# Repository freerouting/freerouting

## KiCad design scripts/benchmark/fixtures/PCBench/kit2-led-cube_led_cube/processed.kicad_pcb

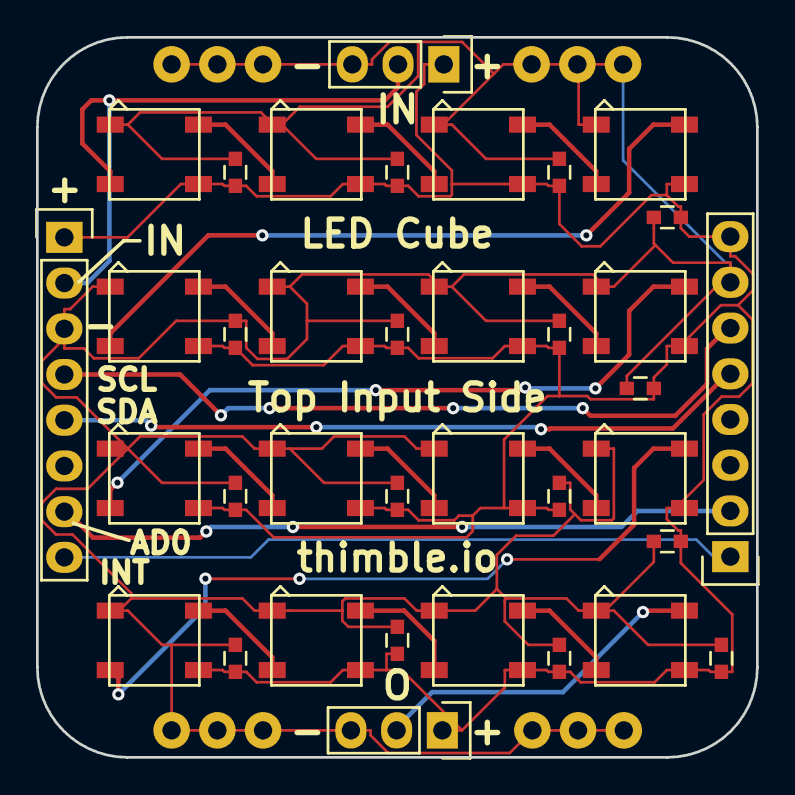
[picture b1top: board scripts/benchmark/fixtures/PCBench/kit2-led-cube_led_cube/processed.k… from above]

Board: 2 copper layers, 40.0 x 40.0 mm, 36 parts (0 on the bottom side), 23 nets.

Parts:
C1, C2, C3, C4, C5, C6, C7, C8, C9, C10, C11, C12, C13, C14, C15, C16: 1uF; C_0603
LED1, LED2, LED3, LED4, LED5, LED6, LED7, LED8, LED9, LED10, LED11, LED12, LED13, LED14, LED15, LED16: LED_RGB_WS2812B; 5050
P1, P4: CONN_01X03; Pin_Header_Straight_1x03
P2, P3: CONN_01X08; Pin_Header_Straight_1x08

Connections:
+5V: C1.1, C2.1, C3.1, C4.1, C5.1, C6.1, C7.1, C8.1, C9.1, C10.1, C11.1, C12.1, C13.1, C14.1, C15.1, C16.1, LED1.1, LED2.1, LED3.1, LED4.1, LED5.1, LED6.1, LED7.1, LED8.1, LED9.1, LED10.1, LED11.1, LED12.1, LED13.1, LED14.1, LED15.1, LED16.1, P1.1, P2.1, P3.8, P4.1
/AD0: P2.7, P3.2
/INT: P2.8, P3.1
/SCL: P2.4, P3.6
/SDA: P2.5, P3.5
GND: C1.2, C2.2, C3.2, C4.2, C5.2, C6.2, C7.2, C8.2, C9.2, C10.2, C11.2, C12.2, C13.2, C14.2, C15.2, C16.2, LED1.3, LED2.3, LED3.3, LED4.3, LED5.3, LED6.3, LED7.3, LED8.3, LED9.3, LED10.3, LED11.3, LED12.3, LED13.3, LED14.3, LED15.3, LED16.3, P1.3, P2.3, P3.7, P4.3
unnamed: LED1.2, LED2.4
unnamed: LED1.4, P1.2, P2.2
unnamed: LED2.2, LED3.4
unnamed: LED3.2, LED4.4
unnamed: LED4.2, LED5.4
unnamed: LED5.2, LED6.4
unnamed: LED6.2, LED7.4
unnamed: LED7.2, LED8.4
unnamed: LED8.2, LED9.4
unnamed: LED10.2, LED11.4
unnamed: LED9.2, LED10.4
unnamed: LED11.2, LED12.4
unnamed: LED12.2, LED13.4
unnamed: LED13.2, LED14.4
unnamed: LED14.2, LED15.4
unnamed: LED15.2, LED16.4
unnamed: LED16.2, P4.2

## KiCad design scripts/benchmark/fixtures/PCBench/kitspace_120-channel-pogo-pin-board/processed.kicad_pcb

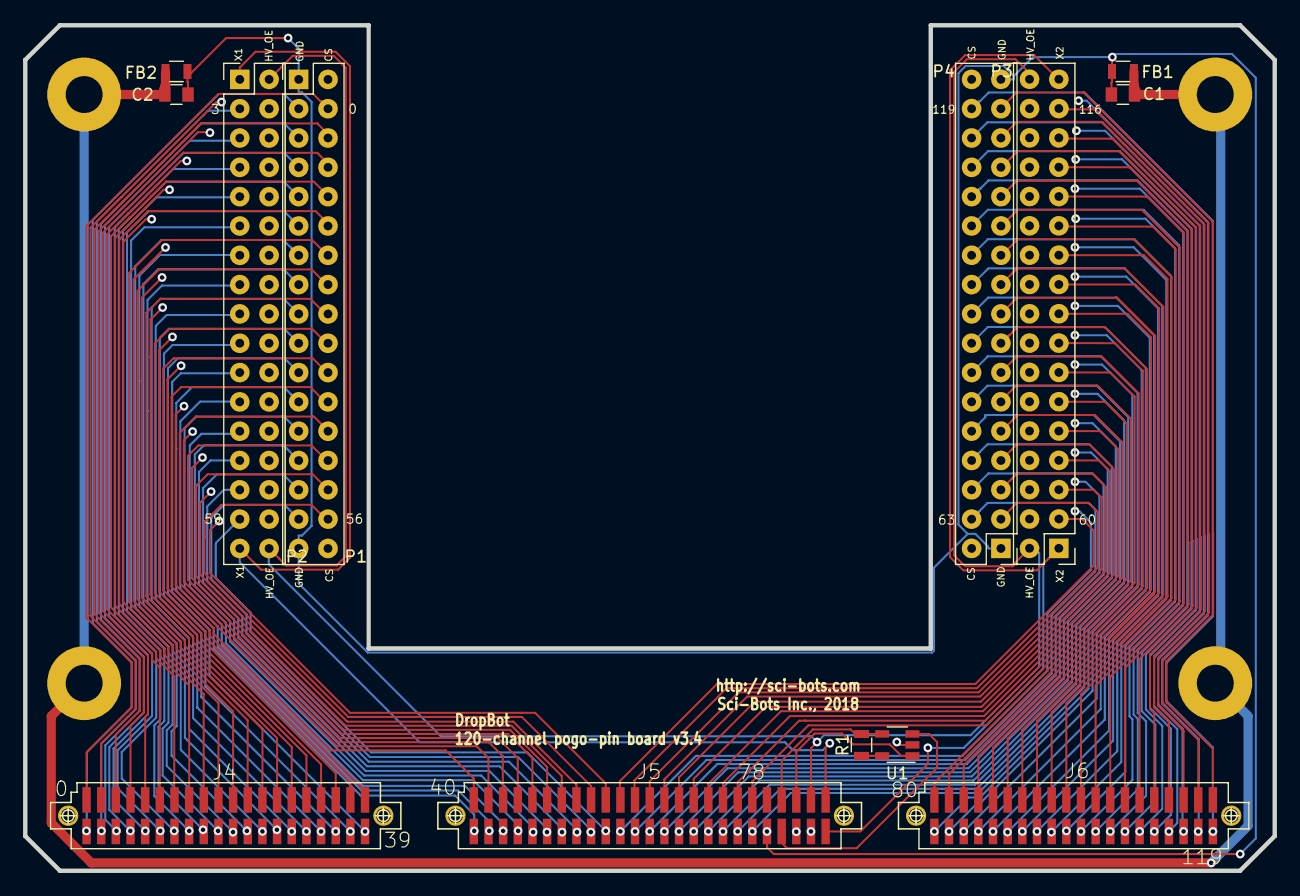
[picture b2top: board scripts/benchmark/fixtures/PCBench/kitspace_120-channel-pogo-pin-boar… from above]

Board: 4 copper layers, 108.2 x 73.2 mm, 17 parts (0 on the bottom side), 130 nets.

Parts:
C1, C2: 0.1uF; C_0805
FB1, FB2: FERRITE; R_0805
J4, J6: SFM-120-02-L-D-A; SFM-120-02-XXX-D-A
J5: SFM-125-02-L-D-A; SFM-125-02-XXX-D-A
P1, P2, P3, P4: Conn_02x17_Odd_Even; Pogo_Pin_Header_Straight_2x17_Pitch2.54mm
P5, P6, P7, P8: CONN_01X01; MountingHole_3.2mm_M3_Pad
R1: 10k; R_0805
U1: CAT24C02TDI; TSOT-23-5

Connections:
+3V3: J5.8, R1.2, U1.4
CH0: J4.40, P1.4
CH1: J4.39, P1.3
CH2: J4.38, P2.4
CH3: J4.37, P2.3
CH4: J4.36, P1.6
CH5: J4.35, P1.5
CH6: J4.34, P2.6
CH7: J4.33, P2.5
CH8: J4.32, P1.8
CH9: J4.31, P1.7
CH10: J4.30, P2.8
CH11: J4.29, P2.7
CH12: J4.28, P1.10
CH13: J4.27, P1.9
CH14: J4.26, P2.10
CH15: J4.25, P2.9
CH16: J4.24, P1.12
CH17: J4.23, P1.11
CH18: J4.22, P2.12
CH19: J4.21, P2.11
CH20: J4.20, P1.14
CH21: J4.19, P1.13
CH22: J4.18, P2.14
CH23: J4.17, P2.13
CH24: J4.16, P1.16
CH25: J4.15, P1.15
CH26: J4.14, P2.16
CH27: J4.13, P2.15
CH28: J4.12, P1.18
CH29: J4.11, P1.17
CH30: J4.10, P2.18
CH31: J4.9, P2.17
CH32: J4.8, P1.20
CH33: J4.7, P1.19
CH34: J4.6, P2.20
CH35: J4.5, P2.19
CH36: J4.4, P1.22
CH37: J4.3, P1.21
CH38: J4.2, P2.22
CH39: J4.1, P2.21
CH40: J5.50, P1.24
CH41: J5.49, P1.23
CH42: J5.48, P2.24
CH43: J5.47, P2.23
CH44: J5.46, P1.26
CH45: J5.45, P1.25
CH46: J5.44, P2.26
CH47: J5.43, P2.25
CH48: J5.42, P1.28
CH49: J5.41, P1.27
CH50: J5.40, P2.28
CH51: J5.39, P2.27
CH52: J5.38, P1.30
CH53: J5.37, P1.29
CH54: J5.36, P2.30
CH55: J5.35, P2.29
CH56: J5.34, P1.32
CH57: J5.33, P1.31
CH58: J5.32, P2.32
CH59: J5.31, P2.31
CH60: J5.30, P3.3
CH61: J5.29, P3.4
CH62: J5.28, P4.3
CH63: J5.27, P4.4
CH64: J5.26, P3.5
CH65: J5.25, P3.6
CH66: J5.24, P4.5
CH67: J5.23, P4.6
CH68: J5.22, P3.7
CH69: J5.21, P3.8
CH70: J5.20, P4.7
CH71: J5.19, P4.8
CH72: J5.18, P3.9
CH73: J5.17, P3.10
CH74: J5.16, P4.9
CH75: J5.15, P4.10
CH76: J5.14, P3.11
CH77: J5.13, P3.12
CH78: J5.12, P4.11
CH79: J5.11, P4.12
CH80: J6.40, P3.13
CH81: J6.39, P3.14
CH82: J6.38, P4.13
CH83: J6.37, P4.14
CH84: J6.36, P3.15
CH85: J6.35, P3.16
CH86: J6.34, P4.15
CH87: J6.33, P4.16
CH88: J6.32, P3.17
CH89: J6.31, P3.18
CH90: J6.30, P4.17
CH91: J6.29, P4.18
CH92: J6.28, P3.19
CH93: J6.27, P3.20
CH94: J6.26, P4.19
CH95: J6.25, P4.20
CH96: J6.24, P3.21
CH97: J6.23, P3.22
CH98: J6.22, P4.21
CH99: J6.21, P4.22
CH100: J6.20, P3.23
CH101: J6.19, P3.24
CH102: J6.18, P4.23
CH103: J6.17, P4.24
CH104: J6.16, P3.25
CH105: J6.15, P3.26
CH106: J6.14, P4.25
CH107: J6.13, P4.26
CH108: J6.12, P3.27
CH109: J6.11, P3.28
CH110: J6.10, P4.27
CH111: J6.9, P4.28
CH112: J6.8, P3.29
CH113: J6.7, P3.30
CH114: J6.6, P4.29
CH115: J6.5, P4.30
CH116: J6.4, P3.31
CH117: J6.3, P3.32
CH118: J6.2, P4.31
CH119: J6.1, P4.32
CH-X1: J5.2, P2.1, P2.33
CH-X2: J5.1, P3.1, P3.33
CHASIS_GND: C1.2, C2.2, FB1.2, FB2.2, P5.1, P6.1, P7.1, P8.1
CUR_SENSE: J5.3, P1.2, P1.34, P4.2, P4.34
GND: C1.1, C2.1, FB1.1, FB2.1, J5.5, J5.9, P1.1, P1.33, P4.1, P4.33, U1.2
HV_OE: J5.4, P2.2, P2.34, P3.2, P3.34
unnamed: R1.1, U1.5
SCL: J5.6, U1.1
SDA: J5.7, U1.3

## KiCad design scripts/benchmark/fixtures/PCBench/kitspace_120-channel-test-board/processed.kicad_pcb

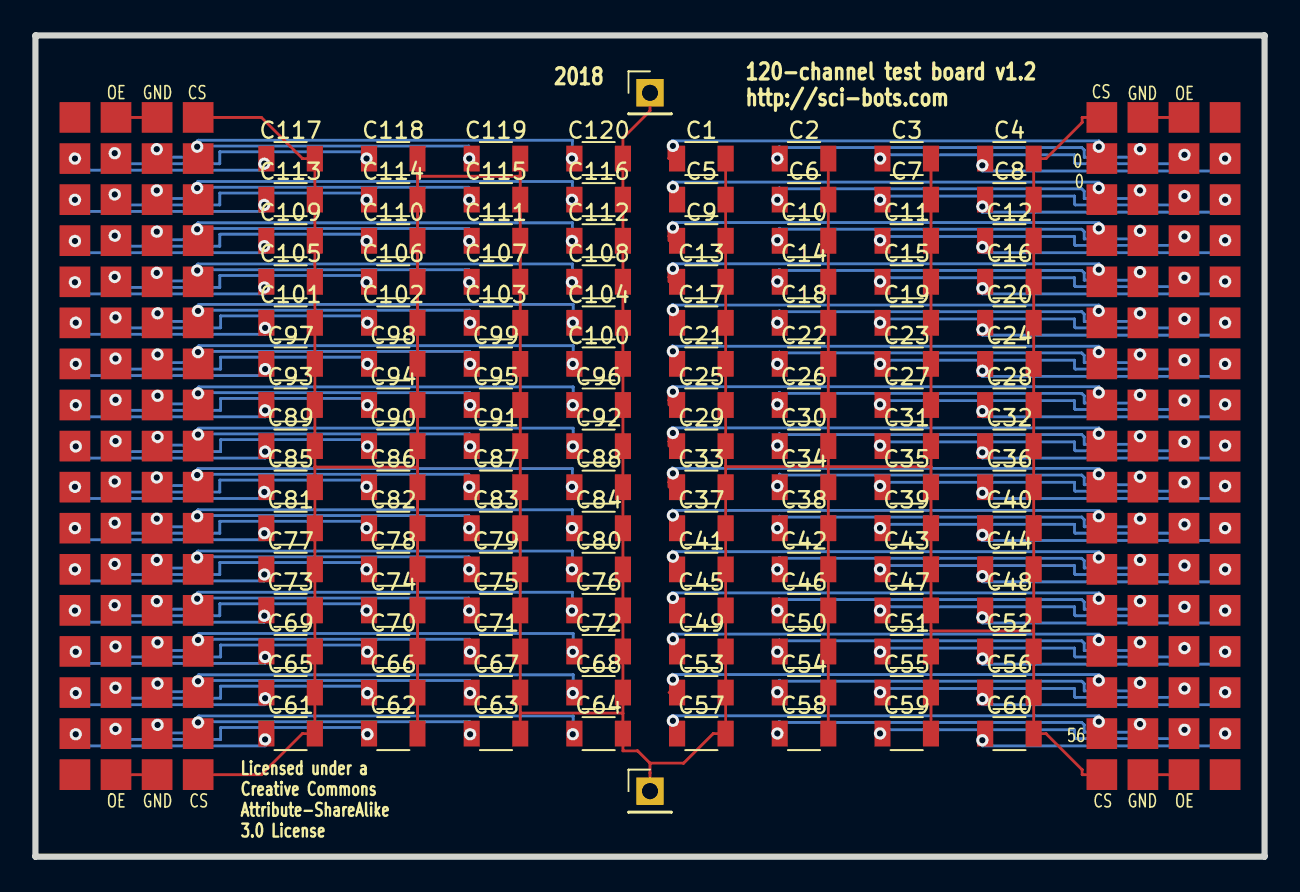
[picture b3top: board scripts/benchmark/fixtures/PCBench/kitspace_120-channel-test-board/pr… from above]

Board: 2 copper layers, 76.0 x 50.8 mm, 258 parts (0 on the bottom side), 125 nets.

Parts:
C1, C2, C3, C4, C5, C6, C7, C8, C9, C10, C11, C12, C13, C14, C15, C16, C17, C18, C19, C20, C21, C22, C23, C24, C25, C26, C27, C28, C29, C30, C31, C32, C33, C34, C35, C36, C37, C38, C39, C40, C41, C42, C43, C44, C45, C46, C47, C48, C49, C50, C51, C52, C53, C54, C55, C56, C57, C58, C59, C60, C61, C62, C63, C64, C65, C66, C67, C68, C69, C70, C71, C72, C73, C74, C75, C76, C77, C78, C79, C80, C81, C82, C83, C84, C85, C86, C87, C88, C89, C90, C91, C92, C93, C94, C95, C96, C97, C98, C99, C100, C101, C102, C103, C104, C105, C106, C107, C108, C109, C110, C111, C112, C113, C114, C115, C116, C117, C118, C119, C120: C; C_1206
P1, P2, P3, P4, P5, P6, P7, P8, P9, P10, P11, P12, P13, P14, P15, P16, P17, P18, P19, P20, P21, P22, P23, P24, P25, P26, P27, P28, P29, P30, P31, P32, P33, P34, P35, P36, P37, P38, P39, P40, P41, P42, P43, P44, P45, P46, P47, P48, P49, P50, P51, P52, P53, P54, P55, P56, P57, P58, P59, P60, P61, P62, P63, P64, P65, P66, P67, P68, P69, P70, P71, P72, P73, P74, P75, P76, P77, P78, P79, P80, P81, P82, P83, P84, P85, P86, P87, P88, P89, P90, P91, P92, P93, P94, P95, P96, P97, P98, P99, P100, P101, P102, P103, P104, P105, P106, P107, P108, P109, P110, P111, P112, P113, P114, P115, P116, P117, P118, P119, P120, P122, P123, P124, P125, P126, P127, P128, P129, P130, P131, P132, P133, P134, P135, P136, P137: CONN_01X01; 1.9mm_DMF_Electrode
P121, P138: CONN_01X01; Pin_Header_Straight_1x01_Pitch2.54mm

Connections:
CUR_SENSE: C1.2, C2.2, C3.2, C4.2, C5.2, C6.2, C7.2, C8.2, C9.2, C10.2, C11.2, C12.2, C13.2, C14.2, C15.2, C16.2, C17.2, C18.2, C19.2, C20.2, C21.2, C22.2, C23.2, C24.2, C25.2, C26.2, C27.2, C28.2, C29.2, C30.2, C31.2, C32.2, C33.2, C34.2, C35.2, C36.2, C37.2, C38.2, C39.2, C40.2, C41.2, C42.2, C43.2, C44.2, C45.2, C46.2, C47.2, C48.2, C49.2, C50.2, C51.2, C52.2, C53.2, C54.2, C55.2, C56.2, C57.2, C58.2, C59.2, C60.2, C61.2, C62.2, C63.2, C64.2, C65.2, C66.2, C67.2, C68.2, C69.2, C70.2, C71.2, C72.2, C73.2, C74.2, C75.2, C76.2, C77.2, C78.2, C79.2, C80.2, C81.2, C82.2, C83.2, C84.2, C85.2, C86.2, C87.2, C88.2, C89.2, C90.2, C91.2, C92.2, C93.2, C94.2, C95.2, C96.2, C97.2, C98.2, C99.2, C100.2, C101.2, C102.2, C103.2, C104.2, C105.2, C106.2, C107.2, C108.2, C109.2, C110.2, C111.2, C112.2, C113.2, C114.2, C115.2, C116.2, C117.2, C118.2, C119.2, C120.2, P121.1, P122.1, P123.1, P124.1, P125.1, P138.1
unnamed: C1.1, P1.1
unnamed: C2.1, P2.1
unnamed: C3.1, P3.1
unnamed: C4.1, P4.1
unnamed: C5.1, P5.1
unnamed: C6.1, P6.1
unnamed: C7.1, P7.1
unnamed: C8.1, P8.1
unnamed: C9.1, P9.1
unnamed: C10.1, P10.1
unnamed: C11.1, P11.1
unnamed: C12.1, P12.1
unnamed: C13.1, P13.1
unnamed: C14.1, P14.1
unnamed: C15.1, P15.1
unnamed: C16.1, P16.1
unnamed: C17.1, P17.1
unnamed: C18.1, P18.1
unnamed: C19.1, P19.1
unnamed: C20.1, P20.1
unnamed: C21.1, P21.1
unnamed: C22.1, P22.1
unnamed: C23.1, P23.1
unnamed: C24.1, P24.1
unnamed: C25.1, P25.1
unnamed: C26.1, P26.1
unnamed: C27.1, P27.1
unnamed: C28.1, P28.1
unnamed: C29.1, P29.1
unnamed: C30.1, P30.1
unnamed: C31.1, P31.1
unnamed: C32.1, P32.1
unnamed: C33.1, P33.1
unnamed: C34.1, P34.1
unnamed: C35.1, P35.1
unnamed: C36.1, P36.1
unnamed: C37.1, P37.1
unnamed: C38.1, P38.1
unnamed: C39.1, P39.1
unnamed: C40.1, P40.1
unnamed: C41.1, P41.1
unnamed: C42.1, P42.1
unnamed: C43.1, P43.1
unnamed: C44.1, P44.1
unnamed: C45.1, P45.1
unnamed: C46.1, P46.1
unnamed: C47.1, P47.1
unnamed: C48.1, P48.1
unnamed: C49.1, P49.1
unnamed: C50.1, P50.1
unnamed: C51.1, P51.1
unnamed: C52.1, P52.1
unnamed: C53.1, P53.1
unnamed: C54.1, P54.1
unnamed: C55.1, P55.1
unnamed: C56.1, P56.1
unnamed: C57.1, P57.1
unnamed: C58.1, P58.1
unnamed: C59.1, P59.1
unnamed: C60.1, P60.1
unnamed: C61.1, P61.1
unnamed: C62.1, P62.1
unnamed: C63.1, P63.1
unnamed: C64.1, P64.1
unnamed: C65.1, P65.1
unnamed: C66.1, P66.1
unnamed: C67.1, P67.1
unnamed: C68.1, P68.1
unnamed: C69.1, P69.1
unnamed: C70.1, P70.1
unnamed: C71.1, P71.1
unnamed: C72.1, P72.1
unnamed: C73.1, P73.1
unnamed: C74.1, P74.1
unnamed: C75.1, P75.1
unnamed: C76.1, P76.1
unnamed: C77.1, P77.1
unnamed: C78.1, P78.1
unnamed: C79.1, P79.1
unnamed: C80.1, P80.1
unnamed: C81.1, P81.1
unnamed: C82.1, P82.1
unnamed: C83.1, P83.1
unnamed: C84.1, P84.1
unnamed: C85.1, P85.1
unnamed: C86.1, P86.1
unnamed: C87.1, P87.1
unnamed: C88.1, P88.1
unnamed: C89.1, P89.1
unnamed: C90.1, P90.1
unnamed: C91.1, P91.1
unnamed: C92.1, P92.1
unnamed: C93.1, P93.1
unnamed: C94.1, P94.1
unnamed: C95.1, P95.1
unnamed: C96.1, P96.1
unnamed: C97.1, P97.1
unnamed: C98.1, P98.1
unnamed: C99.1, P99.1
unnamed: C100.1, P100.1
unnamed: C101.1, P101.1
unnamed: C102.1, P102.1
unnamed: C103.1, P103.1
unnamed: C104.1, P104.1
unnamed: C105.1, P105.1
unnamed: C106.1, P106.1
unnamed: C107.1, P107.1
unnamed: C108.1, P108.1
unnamed: C109.1, P109.1
unnamed: C110.1, P110.1
unnamed: C111.1, P111.1
unnamed: C112.1, P112.1
unnamed: C113.1, P113.1
unnamed: C114.1, P114.1
unnamed: C115.1, P115.1
unnamed: C116.1, P116.1
unnamed: C117.1, P117.1
unnamed: C118.1, P118.1
unnamed: C119.1, P119.1
unnamed: C120.1, P120.1
unnamed: P126.1, P127.1
unnamed: P128.1, P129.1
unnamed: P130.1, P131.1
unnamed: P132.1, P133.1

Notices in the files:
scripts/benchmark/fixtures/PCBench/kitspace_120-channel-test-board/processed.kicad_pcb:
Licensed under a
Creative Commons
Attribute-ShareAlike
